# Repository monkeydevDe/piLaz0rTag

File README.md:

# piLaz0rTag

Goto /hardware for fritzing stuff

Goto /code for SourceCode

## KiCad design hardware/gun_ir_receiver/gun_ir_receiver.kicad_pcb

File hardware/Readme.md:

# Hardware

## Shopping List:

* Pi Zero W
* Logic level Converter *https://www.sparkfun.com/products/12009*
* **

## Folders

* **prototype**: Here are the schematics done with fritzing for the breadboard testing.
* **ir_receiver**: Ir receiver module schematics.
* **ir_sender**: Ir sender module schematics.
* **main_board**: Pi Hat module schematics.
* **pi_header**: Template for a pi header.

## Schematics

The schematics are done with the awesome Tool: http://fritzing.org for the prototyping and KiCad for the PCB design.

### Part libraries we used

#### KiCad

* Take a look here: https://kicad.github.io/ !!!!
* As a base for the PL9823 LEDs: https://github.com/madworm/WS2812B.pretty.git
* For the some parts https://github.com/RoboUlbricht/kicad.lib.git
* PiZero hat: https://github.com/help-14/PiZeroHat
* 74AHCT125: https://github.com/propane-and-electrons/kicad-libs
* https://github.com/cfobel/sparkfun_kicad_lib
* https://github.com/benwis/SparkFun-Kicad-Libraries (includes moste of the sparkfun stuff)
* https://www.snapeda.com/parts/L293D/STMicroelectronics/view-part/
* Search for parts: https://easyeda.com/search/level%20bidirectional

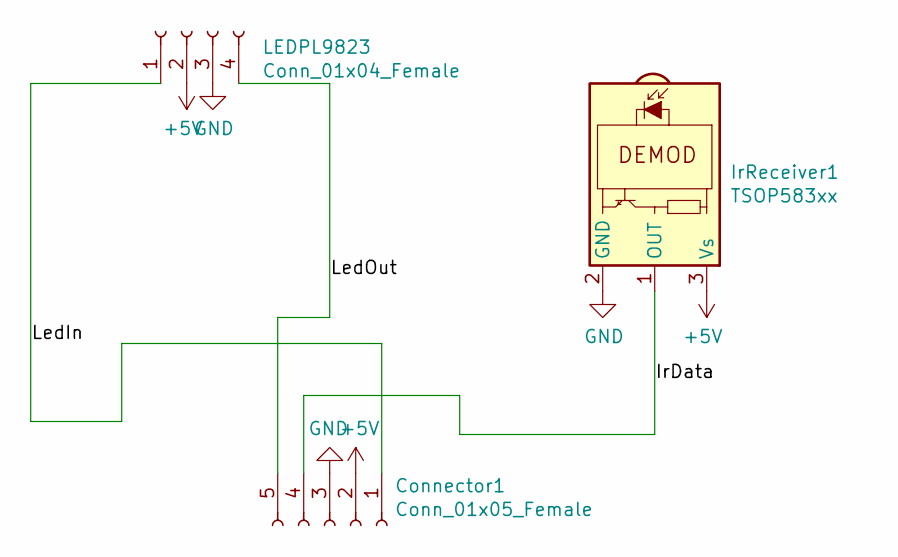
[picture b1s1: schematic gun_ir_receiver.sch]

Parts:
Connector1: Conn_01x05_Female; JST_EH_B05B-EH-A_1x05_P2.50mm_Vertical
IrReceiver1: TSOP583xx; Vishay_MINICAST-3Pin
LEDPL9823: Conn_01x04_Female; PinSocket_1x04_P2.54mm_Vertical

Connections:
+5V: Connector1.2, IrReceiver1.3 (Vs), LEDPL9823.2
/IrData: Connector1.4, IrReceiver1.1 (OUT)
/LedIn: Connector1.1, LEDPL9823.1
/LedOut: Connector1.5, LEDPL9823.4
GND: Connector1.3, IrReceiver1.2 (GND), LEDPL9823.3

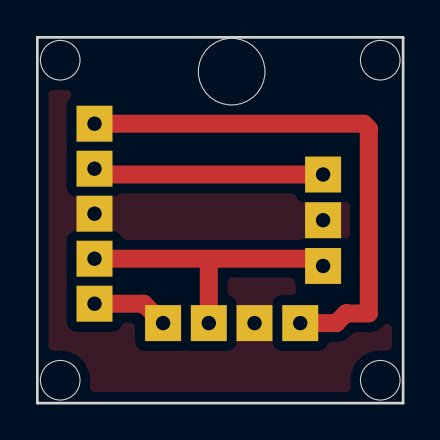
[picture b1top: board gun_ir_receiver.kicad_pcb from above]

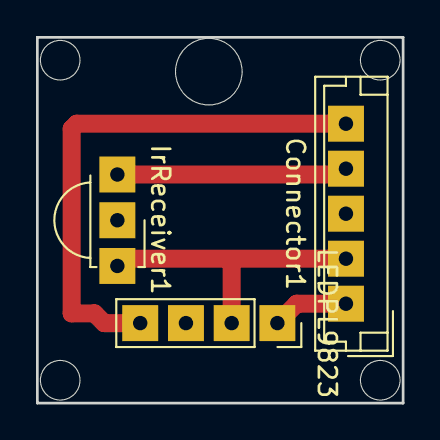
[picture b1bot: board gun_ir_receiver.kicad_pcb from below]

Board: 2 copper layers, 20.3 x 20.3 mm, 6 parts (3 on the bottom side), 5 nets.

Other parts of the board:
Cable Hole: MountingHole_3.7mm
M2, M2#2: MountingHole_2.2mm_M2

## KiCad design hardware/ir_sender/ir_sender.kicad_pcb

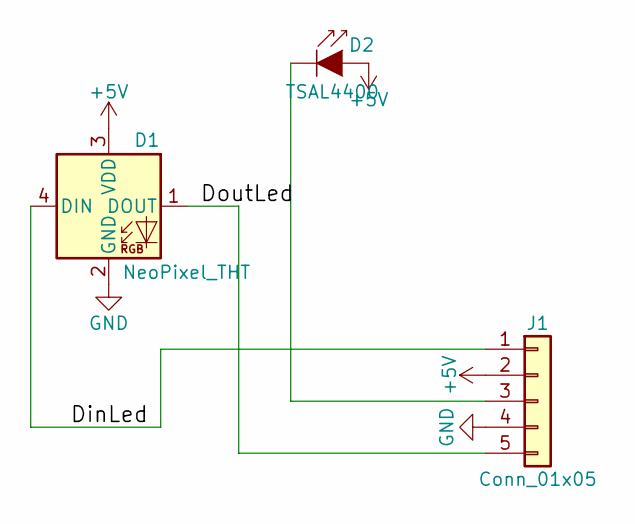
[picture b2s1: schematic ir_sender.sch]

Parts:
D1: NeoPixel_THT; Socket_Strip_Straight_1x04_Pitch2.54mm
D2: TSAL4400; Socket_Strip_Straight_1x02_Pitch2.54mm
J1: Conn_01x05; JST_XH_B05B-XH-A_05x2.50mm_Straight

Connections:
+5V: D1.3 (VDD), D2.2 (A), J1.2
/DinLed: D1.4 (DIN), J1.1
/DoutLed: D1.1 (DOUT), J1.5
GND: D1.2 (GND), J1.4
unnamed: D2.1 (K), J1.3

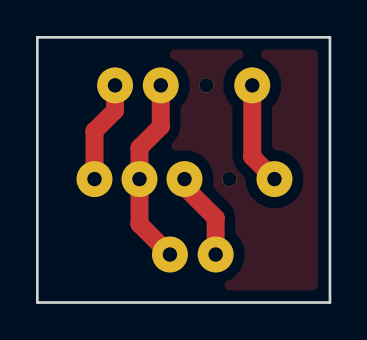
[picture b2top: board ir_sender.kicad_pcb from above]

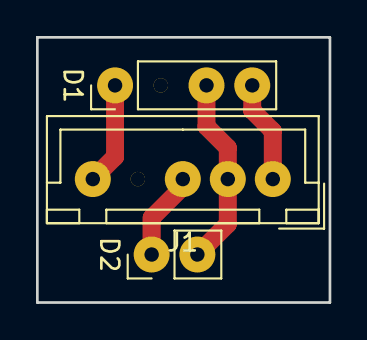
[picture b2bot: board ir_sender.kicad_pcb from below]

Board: 2 copper layers, 16.3 x 14.7 mm, 3 parts (3 on the bottom side), 5 nets.

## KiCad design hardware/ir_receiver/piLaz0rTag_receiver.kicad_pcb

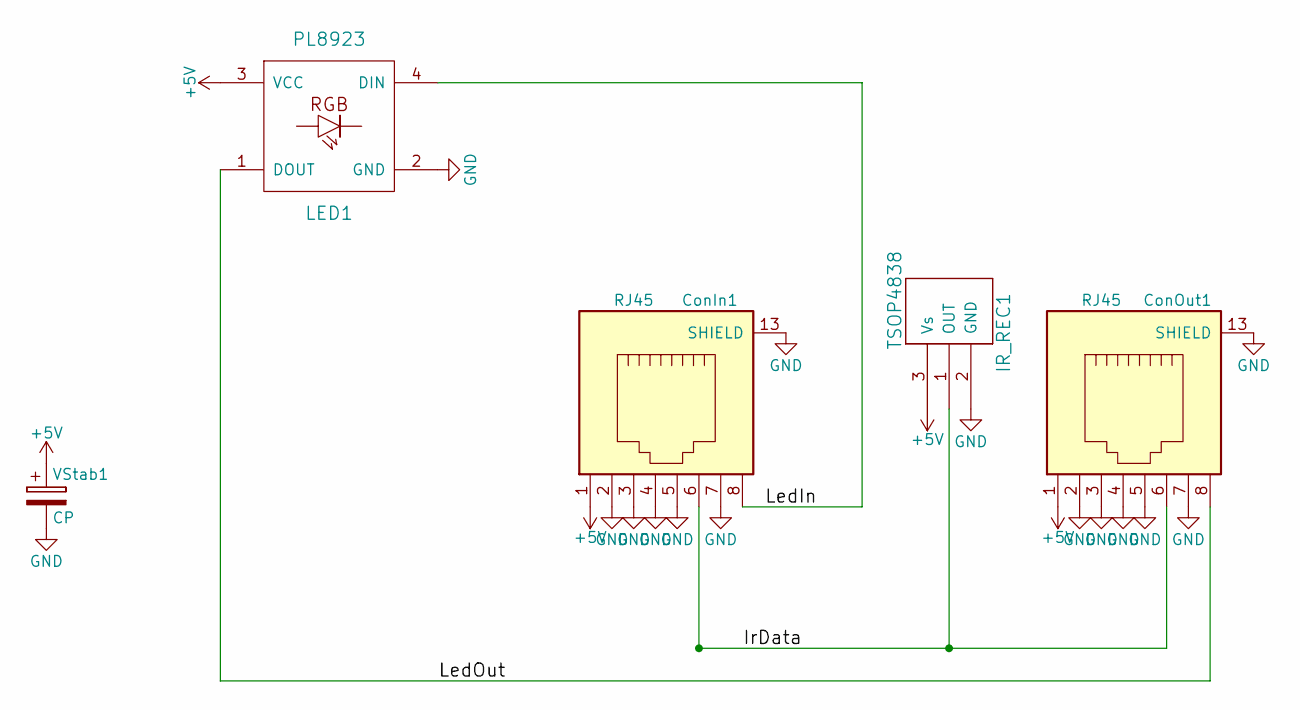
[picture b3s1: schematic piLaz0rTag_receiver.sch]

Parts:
ConIn1: RJ45; rj45-seppel-small
ConOut1: RJ45; rj45-seppel-small
IR_REC1: TSOP4838; IRReceiver_Vishay_MOLD-3pin
LED1: PL8923; Socket_Strip_Straight_1x04_Pitch2.54mm
VStab1: CP; CP_Radial_D4.0mm_P2.00mm

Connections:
+5V: ConIn1.1, ConOut1.1, IR_REC1.3 (Vs), LED1.3 (VCC), VStab1.1
/IrData: ConIn1.6, ConOut1.6, IR_REC1.1 (OUT)
/LedIn: ConIn1.8, LED1.4 (DIN)
/LedOut: ConOut1.8, LED1.1 (DOUT)
GND: ConIn1.2, ConIn1.3, ConIn1.4, ConIn1.5, ConIn1.7, ConIn1.13 (SHIELD), ConOut1.2, ConOut1.3, ConOut1.4, ConOut1.5, ConOut1.7, ConOut1.13 (SHIELD), IR_REC1.2 (GND), LED1.2 (GND), VStab1.2

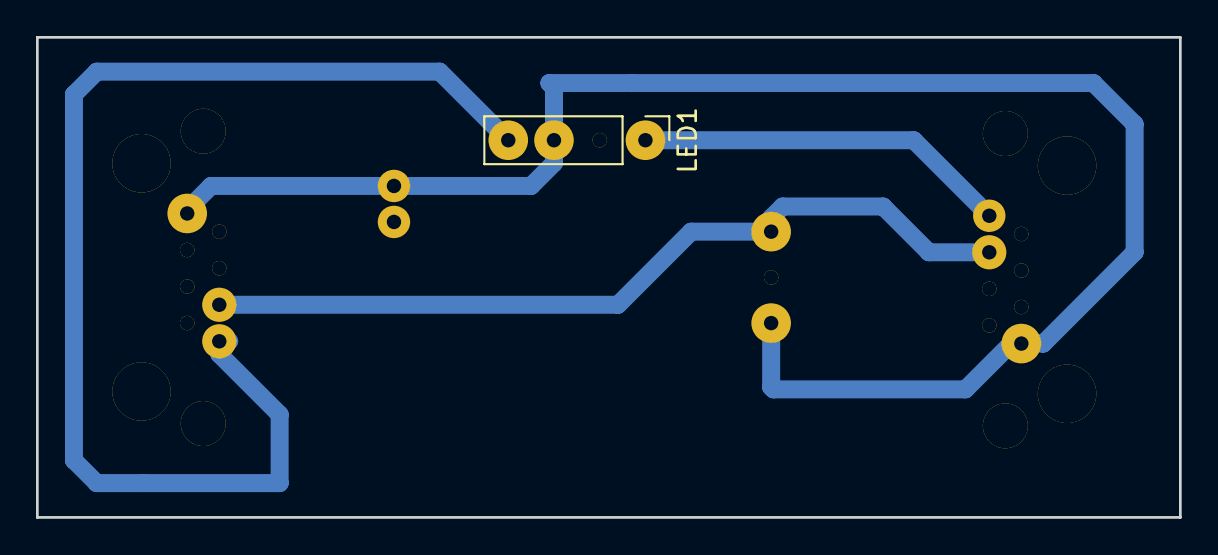
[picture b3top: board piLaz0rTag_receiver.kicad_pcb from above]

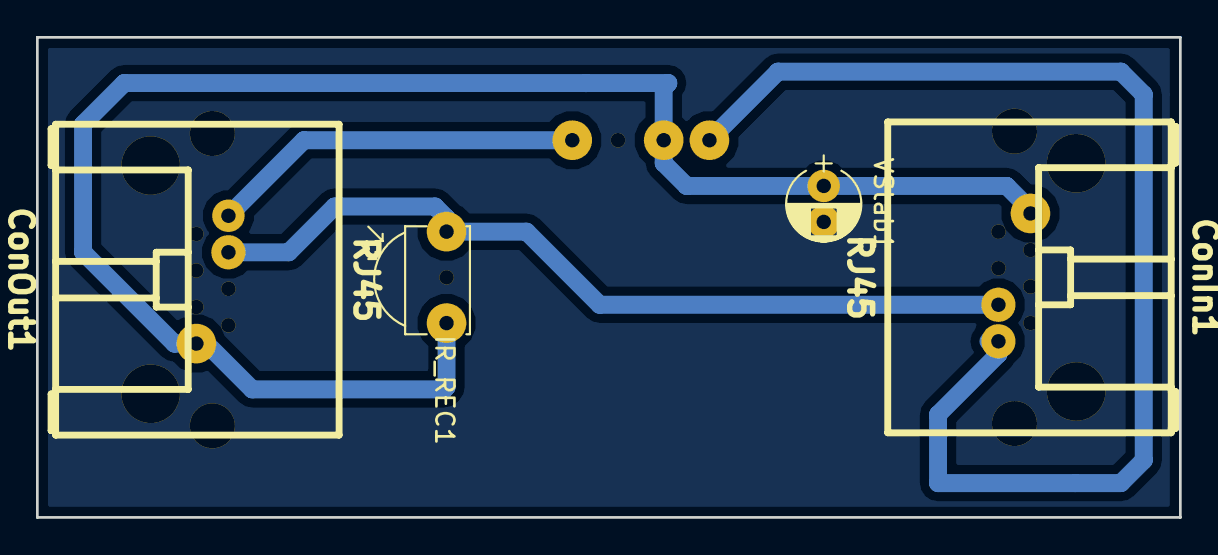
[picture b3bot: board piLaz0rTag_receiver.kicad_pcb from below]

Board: 2 copper layers, 63.5 x 26.7 mm, 5 parts (4 on the bottom side), 5 nets.

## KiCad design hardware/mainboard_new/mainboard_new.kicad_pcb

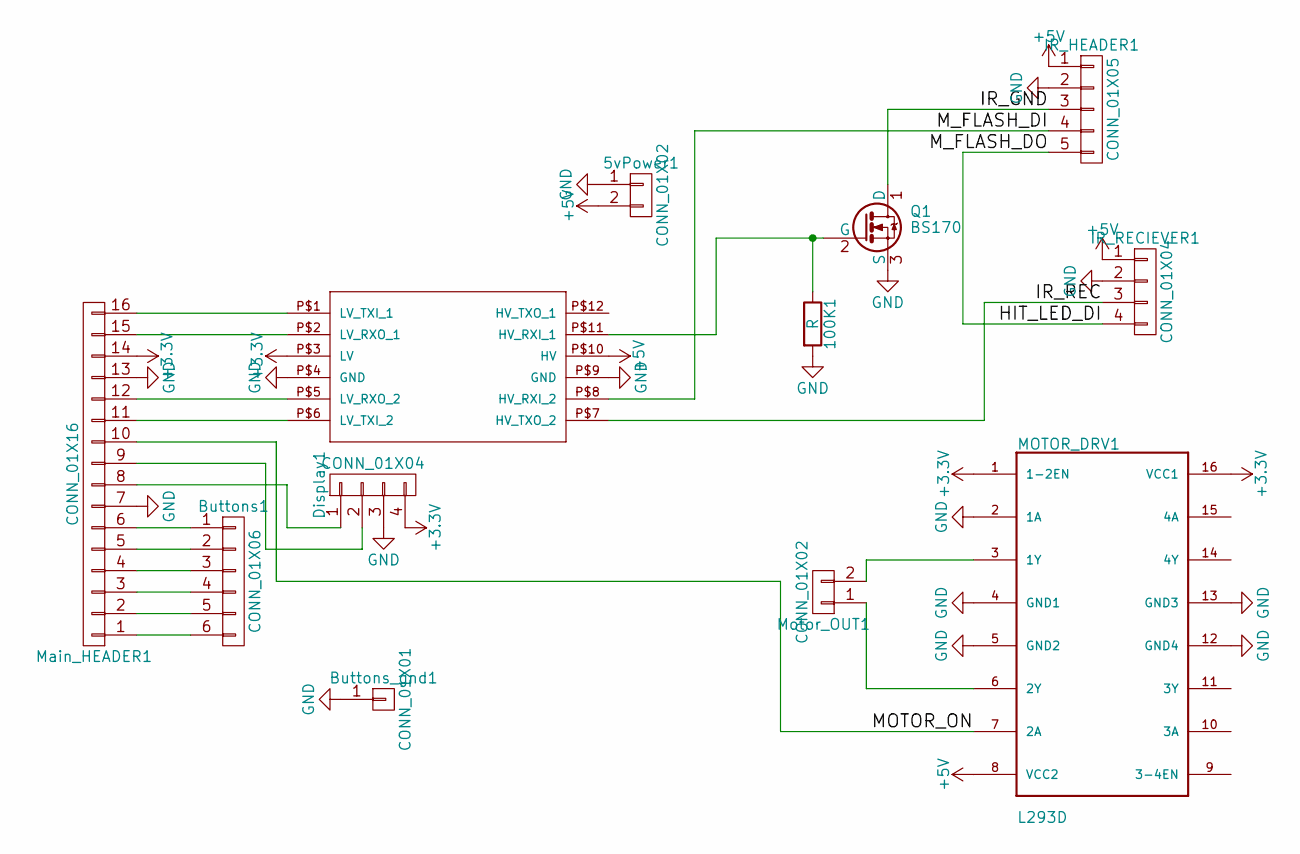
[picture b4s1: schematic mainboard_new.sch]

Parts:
5vPower1: CONN_01X02; JST_EH_B02B-EH-A_02x2.50mm_Straight
100K1: R; R_Axial_DIN0207_L6.3mm_D2.5mm_P10.16mm_Horizontal
Buttons1: CONN_01X06; JST_EH_B06B-EH-A_06x2.50mm_Straight
Buttons_gnd1: CONN_01X01; Socket_Strip_Straight_1x01_Pitch1.27mm
Display1: CONN_01X04; JST_EH_B04B-EH-A_04x2.50mm_Straight
IR_HEADER1: CONN_01X05; JST_EH_B05B-EH-A_05x2.50mm_Straight
IR_RECIEVER1: CONN_01X04; JST_EH_B04B-EH-A_04x2.50mm_Straight
M1: LOGIC_LEVEL_CONVERTER
MOTOR_DRV1: L293D; DIL16
Main_HEADER1: CONN_01X16; Socket_Strip_Straight_1x16_Pitch2.54mm
Motor_OUT1: CONN_01X02; Socket_Strip_Straight_1x02_Pitch2.54mm
Q1: BS170; TO-92_Inline_Wide

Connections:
+3V3: Display1.4, M1.P$3 (LV), MOTOR_DRV1.1 (1-2EN), MOTOR_DRV1.16 (VCC1), Main_HEADER1.14
+5V: 5vPower1.2, IR_HEADER1.1, IR_RECIEVER1.1, M1.P$10 (HV), MOTOR_DRV1.8 (VCC2)
/HIT_LED_DI: IR_HEADER1.5, IR_RECIEVER1.4
/IR_GND: IR_HEADER1.3, Q1.1 (D)
/IR_REC: IR_RECIEVER1.3, M1.P$7 (HV_TXO_2)
/MOTOR_ON: MOTOR_DRV1.7 (2A), Main_HEADER1.10
/M_FLASH_DI: IR_HEADER1.4, M1.P$8 (HV_RXI_2)
GND: 5vPower1.1, 100K1.2, Buttons_gnd1.1, Display1.3, IR_HEADER1.2, IR_RECIEVER1.2, M1.P$4 (GND), M1.P$9 (GND), MOTOR_DRV1.2 (1A), MOTOR_DRV1.4 (GND1), MOTOR_DRV1.5 (GND2), MOTOR_DRV1.12 (GND4), MOTOR_DRV1.13 (GND3), Main_HEADER1.7, Main_HEADER1.13, Q1.3 (S)
unnamed: 100K1.1, M1.P$11 (HV_RXI_1), Q1.2 (G)
unnamed: Buttons1.1, Main_HEADER1.6
unnamed: Buttons1.2, Main_HEADER1.5
unnamed: Buttons1.3, Main_HEADER1.4
unnamed: Buttons1.4, Main_HEADER1.3
unnamed: Buttons1.5, Main_HEADER1.2
unnamed: Buttons1.6, Main_HEADER1.1
unnamed: Display1.1, Main_HEADER1.8
unnamed: Display1.2, Main_HEADER1.9
unnamed: M1.P$1 (LV_TXI_1), Main_HEADER1.16
unnamed: M1.P$2 (LV_RXO_1), Main_HEADER1.15
unnamed: M1.P$5 (LV_RXO_2), Main_HEADER1.12
unnamed: M1.P$6 (LV_TXI_2), Main_HEADER1.11
unnamed: MOTOR_DRV1.3 (1Y), Motor_OUT1.2
unnamed: MOTOR_DRV1.6 (2Y), Motor_OUT1.1

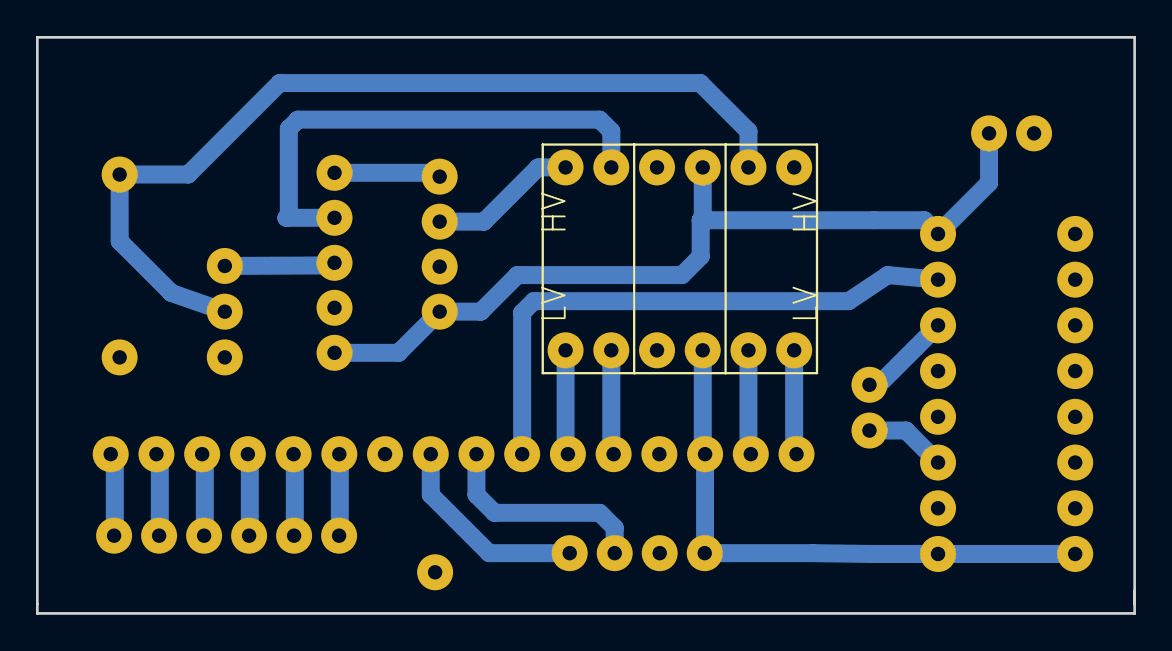
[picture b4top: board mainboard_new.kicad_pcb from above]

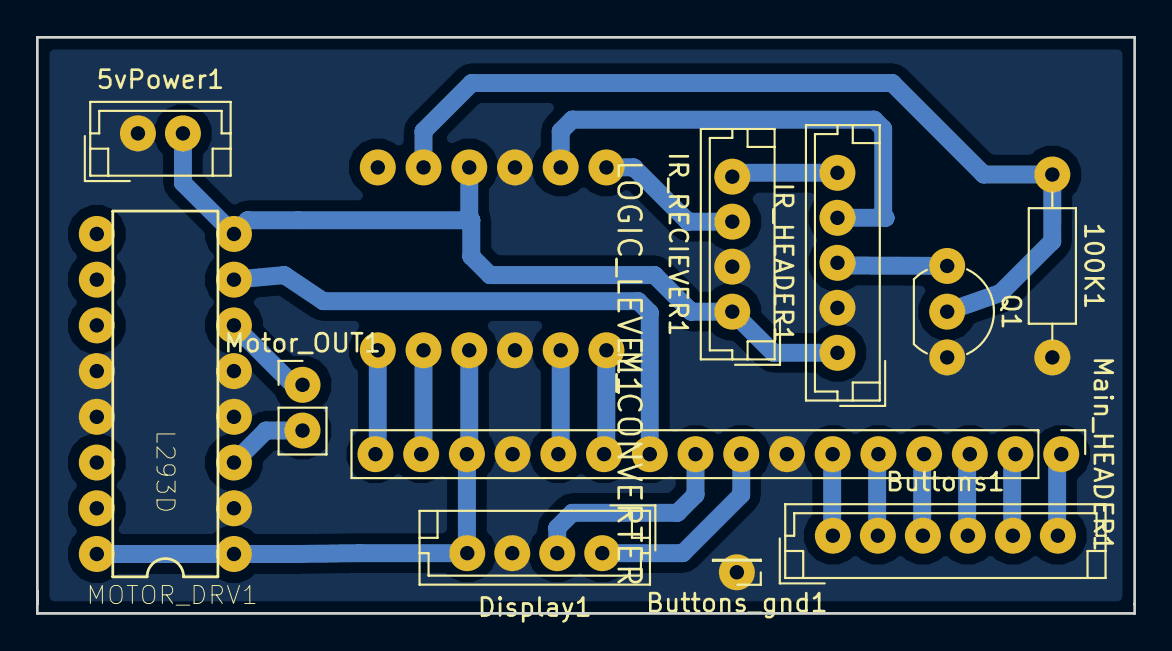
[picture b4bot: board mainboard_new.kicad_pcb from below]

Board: 2 copper layers, 61.0 x 32.0 mm, 12 parts (12 on the bottom side), 23 nets.

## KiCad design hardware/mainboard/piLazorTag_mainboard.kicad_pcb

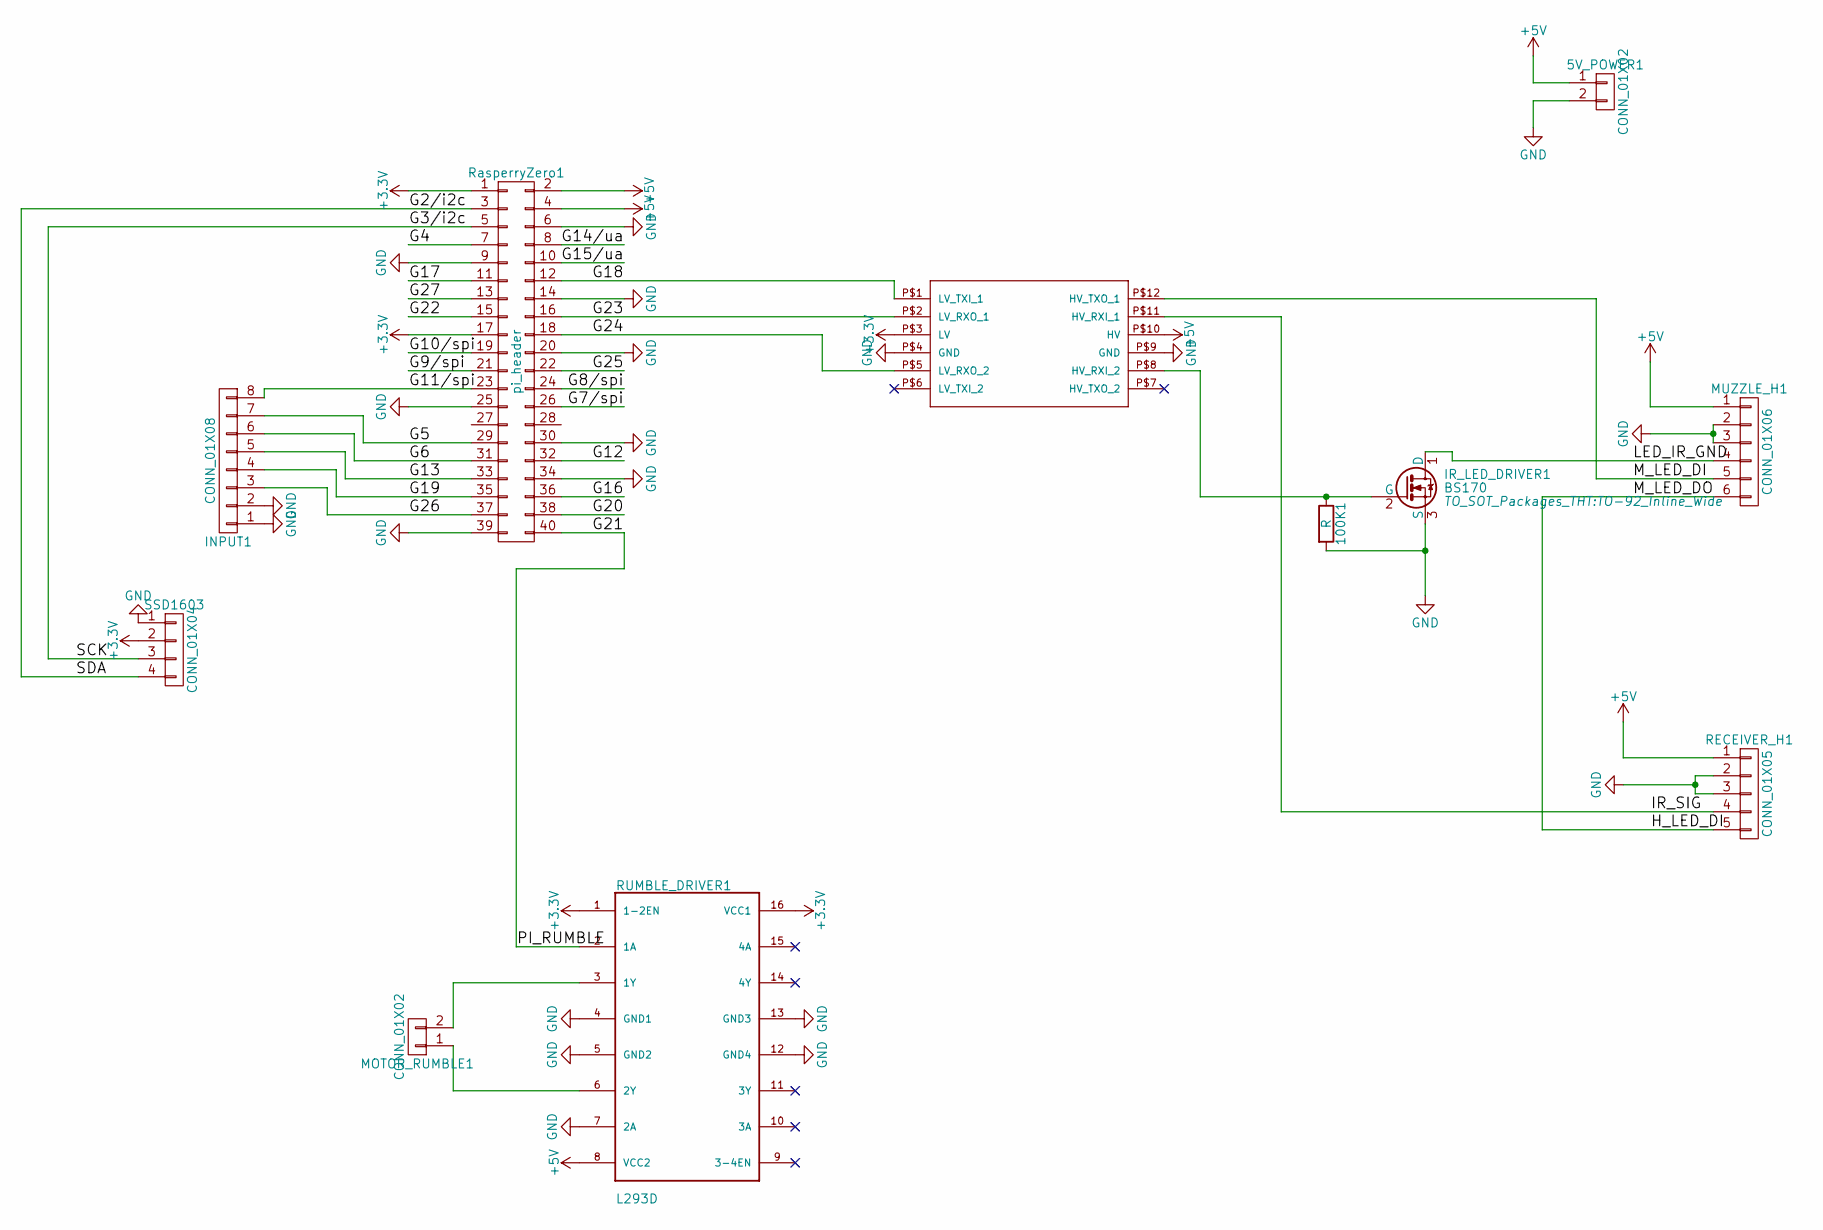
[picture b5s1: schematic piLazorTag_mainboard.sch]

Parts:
5V_POWER1: CONN_01X02; Pin_Header_Straight_2x01_Pitch2.54mm
100K1: R; R_Axial_DIN0207_L6.3mm_D2.5mm_P10.16mm_Horizontal
INPUT1: CONN_01X08; Pin_Header_Straight_1x08_Pitch2.54mm
IR_LED_DRIVER1: BS170; TO-92_Inline_Wide
M1: LOGIC_LEVEL_CONVERTER
MOTOR_RUMBLE1: CONN_01X02; Pin_Header_Straight_1x02_Pitch2.54mm
MUZZLE_H1: CONN_01X06; Pin_Header_Straight_1x06_Pitch2.54mm
RECEIVER_H1: CONN_01X05; Pin_Header_Straight_1x05_Pitch2.54mm
RUMBLE_DRIVER1: L293D; DIL16
RasperryZero1: pi_header; Pin_Header_Straight_2x20_Pitch2.54mm
SSD1603: CONN_01X04; Pin_Header_Straight_1x04_Pitch2.54mm

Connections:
+3V3: M1.P$3 (LV), RUMBLE_DRIVER1.1 (1-2EN), RUMBLE_DRIVER1.16 (VCC1), RasperryZero1.1, RasperryZero1.17, SSD1603.2
+5V: 5V_POWER1.1, M1.P$10 (HV), MUZZLE_H1.1, RECEIVER_H1.1, RUMBLE_DRIVER1.8 (VCC2), RasperryZero1.2, RasperryZero1.4
/G2/i2c: RasperryZero1.3, SSD1603.4
/G3/i2c: RasperryZero1.5, SSD1603.3
/G4: RasperryZero1.7
/G5: INPUT1.7, RasperryZero1.29
/G6: INPUT1.6, RasperryZero1.31
/G7/spi: RasperryZero1.26
/G8/spi: RasperryZero1.24
/G9/spi: RasperryZero1.21
/G10/spi: RasperryZero1.19
/G11/spi: INPUT1.8, RasperryZero1.23
/G12: RasperryZero1.32
/G13: INPUT1.5, RasperryZero1.33
/G14/ua: RasperryZero1.8
/G15/ua: RasperryZero1.10
/G16: RasperryZero1.36
/G17: RasperryZero1.11
/G18: M1.P$1 (LV_TXI_1), RasperryZero1.12
/G19: INPUT1.4, RasperryZero1.35
/G20: RasperryZero1.38
/G21: RUMBLE_DRIVER1.2 (1A), RasperryZero1.40
/G22: RasperryZero1.15
/G23: M1.P$2 (LV_RXO_1), RasperryZero1.16
/G24: M1.P$5 (LV_RXO_2), RasperryZero1.18
/G25: RasperryZero1.22
/G26: INPUT1.3, RasperryZero1.37
/G27: RasperryZero1.13
/H_LED_DI: MUZZLE_H1.6, RECEIVER_H1.5
/IR_SIG: M1.P$11 (HV_RXI_1), RECEIVER_H1.4
/LED_IR_GND: IR_LED_DRIVER1.1 (D), MUZZLE_H1.4
/M_LED_DI: M1.P$12 (HV_TXO_1), MUZZLE_H1.5
GND: 5V_POWER1.2, 100K1.2, INPUT1.1, INPUT1.2, IR_LED_DRIVER1.3 (S), M1.P$4 (GND), M1.P$9 (GND), MUZZLE_H1.2, MUZZLE_H1.3, RECEIVER_H1.2, RECEIVER_H1.3, RUMBLE_DRIVER1.4 (GND1), RUMBLE_DRIVER1.5 (GND2), RUMBLE_DRIVER1.7 (2A), RUMBLE_DRIVER1.12 (GND4), RUMBLE_DRIVER1.13 (GND3), RasperryZero1.6, RasperryZero1.9, RasperryZero1.14, RasperryZero1.20, RasperryZero1.25, RasperryZero1.30, RasperryZero1.34, RasperryZero1.39, SSD1603.1
unnamed: 100K1.1, IR_LED_DRIVER1.2 (G), M1.P$8 (HV_RXI_2)
unnamed: MOTOR_RUMBLE1.1, RUMBLE_DRIVER1.6 (2Y)
unnamed: MOTOR_RUMBLE1.2, RUMBLE_DRIVER1.3 (1Y)

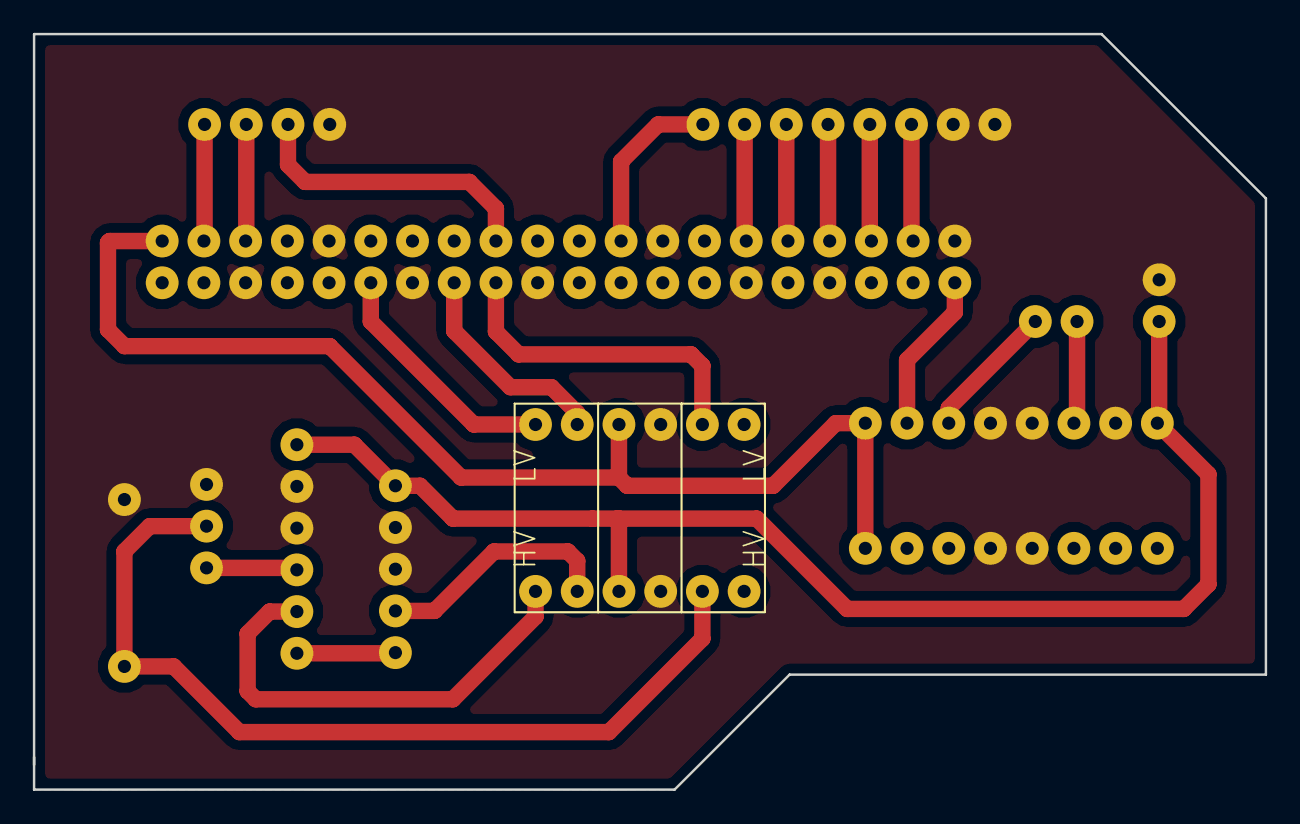
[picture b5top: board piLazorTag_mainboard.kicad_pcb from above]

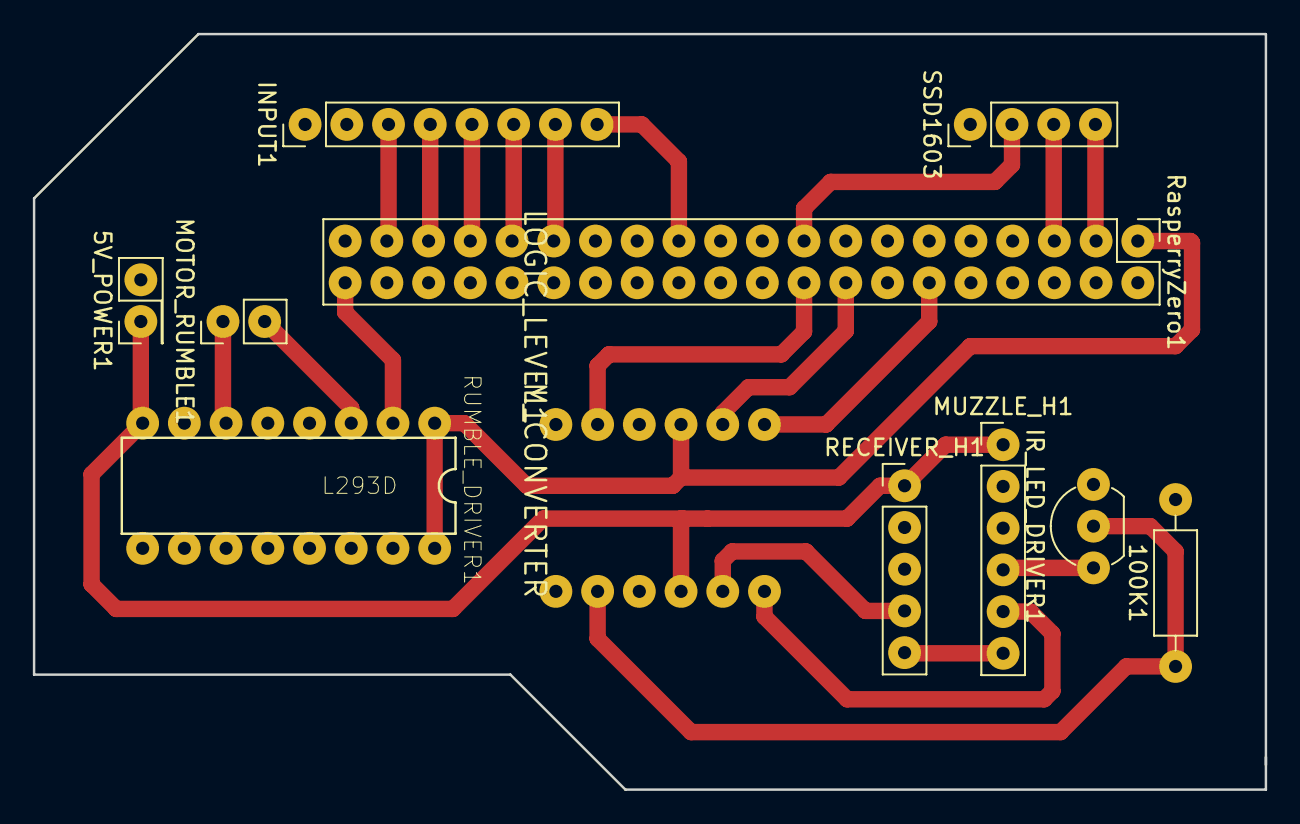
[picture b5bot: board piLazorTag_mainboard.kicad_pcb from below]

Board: 2 copper layers, 75.0 x 46.0 mm, 11 parts (11 on the bottom side), 22 nets.

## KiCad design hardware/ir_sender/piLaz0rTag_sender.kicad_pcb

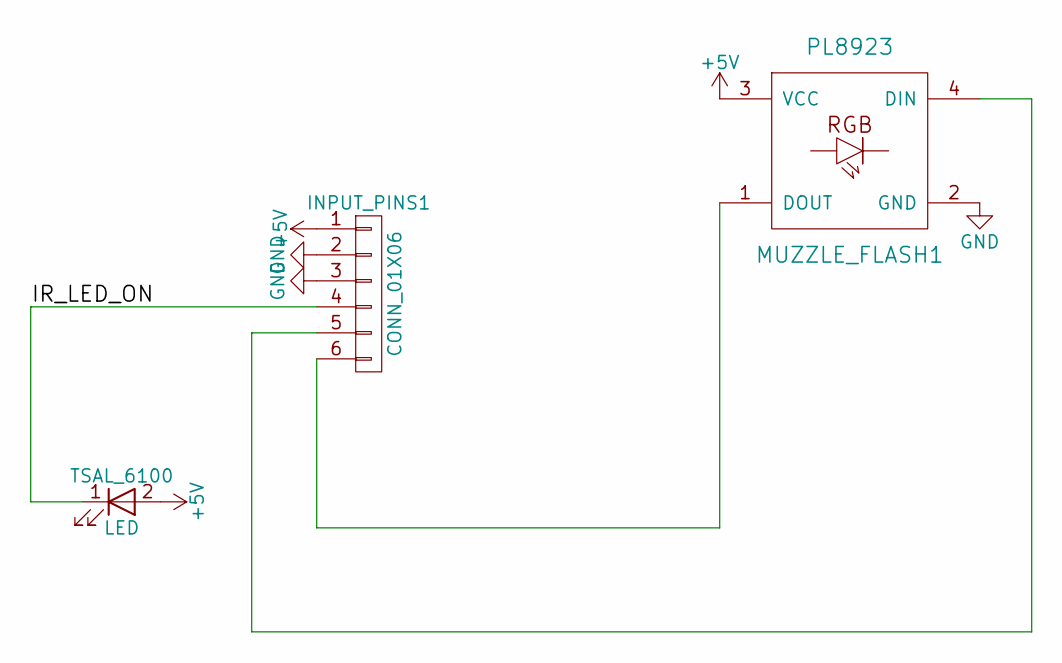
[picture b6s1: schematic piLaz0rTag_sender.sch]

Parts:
INPUT_PINS1: CONN_01X06; Socket_Strip_Straight_1x06_Pitch2.54mm
MUZZLE_FLASH1: PL8923; Socket_Strip_Straight_1x04_Pitch2.54mm
TSAL_6100: LED; LED_D5.0mm

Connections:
+5V: INPUT_PINS1.1, MUZZLE_FLASH1.3 (VCC), TSAL_6100.2 (A)
/IR_LED_ON: INPUT_PINS1.4, TSAL_6100.1 (K)
GND: INPUT_PINS1.2, INPUT_PINS1.3, MUZZLE_FLASH1.2 (GND)
unnamed: INPUT_PINS1.5, MUZZLE_FLASH1.4 (DIN)
unnamed: INPUT_PINS1.6, MUZZLE_FLASH1.1 (DOUT)

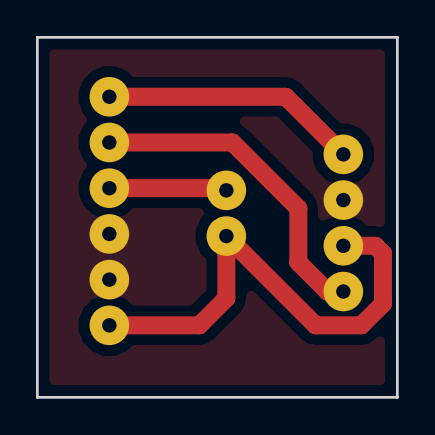
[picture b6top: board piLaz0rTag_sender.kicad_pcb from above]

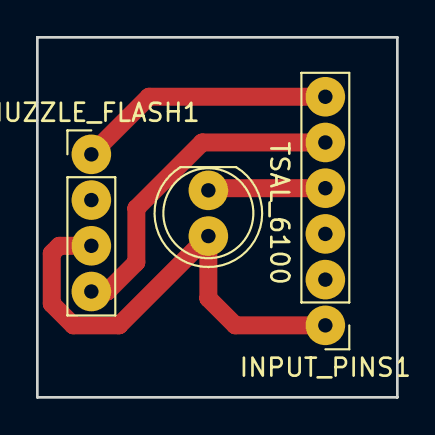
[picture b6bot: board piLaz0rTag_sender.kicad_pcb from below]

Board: 2 copper layers, 20.0 x 20.0 mm, 3 parts (3 on the bottom side), 5 nets.

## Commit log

2017-03-25 Start to add strucuture
2017-03-25 Add first gun schemantic
2017-03-25 Add the first breadboard layout
2017-03-30 add folder n structure for code add gitignore add settings.js module add display.js module add primary js -> piLaz0rTag.js
2017-04-05 add standard.js for defining enum like values for global use, add logging.js for simple custom app logging, change display.js to use a parent display obj to display.js with prototypes change display.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
2017-04-07 add standards about game actions + Menu events add standards about device stats
2017-04-07 add primary vars and extend init of event handling
2017-04-07 add display prototype init initial menu to display.js add menuHandler to piLaz0rTag.js
2017-04-07 add some commas
2017-04-10 Some documentation added
2017-04-10 Add package json
2017-04-10 Add rpi-ws281x-native as node dependency
2017-04-10 Add nodemon
2017-04-10 Add start via nodemon
2017-04-10 Add missing ,
2017-04-10 Add https://github.com/NeinsKnull/oled_ssd1306_i2c as dependency
2017-04-10 Add some basic keyboard handler
2017-04-11 change comments (cosmetic)
2017-04-11 add the ParentDisplay.prototype functionality to init an initial menu an print the screen for display
2017-04-12 Add test lircd.conf using milestag protocoll
2017-04-12 Removed ending space so it can be parsed by lircd.
2017-04-12 Add a functional test lircd file
2017-04-12 #1 start implementing the lircd.conf generator
2017-04-12 #1 Generate the correct hex codes
2017-04-12 #1 Add some documentation
2017-04-12 #1 Add a .gitignore file for the generated file
2017-04-12 #1 Add a Readme.md for the tool
2017-04-12 #2 Start to implement a lircd handler
2017-04-13 #2 Start to change to es6
2017-04-13 #2 Better es6 class handling
2017-04-13 #2 Add winston as logger
2017-04-13 #2 Add description for soundcard setup
2017-04-14 #2 first try with audio not so good so far
2017-04-14 #4 Add Weberser and move some modules to singleton
2017-04-14 #4 refactor the input libary to get web ready
2017-04-14 #4 Start to add socket.io
2017-04-14 #4 We can shot now via websocket
2017-04-14 #4 IR data sending is now better
2017-04-14 #4 Shoot now triggers from web socket to ir :)
2017-04-14 Make the logger level setable in a config
2017-04-15 #6 Start to add the game deathmatch
2017-04-15 #6 Reloading and Shooting is working rudamantary
2017-04-15 #6 Simple webfrontend is getting done
2017-04-15 #6 Reloading works now
2017-04-15 #6 Better web view for the data
2017-04-15 #6 Some cleanup
2017-04-15 #6 Hit is now handled
2017-04-15 #6 Add a simple respawn mechamism
2017-04-15 #6 Better player status handling
2017-04-15 #6 POC for teamdeathmacht mode
2017-04-15 #6 add a game setup html page
2017-04-15 #6 Start the game via the webinterface
2017-04-15 #6 Start game is working now
2017-04-15 #6 Start and stop game over events
2017-04-15 #6 Started adding LEDS
2017-04-17 add a ir mock
2017-04-17 add instance to the sendShootMsg in IrMockHandler
2017-04-18 #11 Start pcb layout for ir receiver
2017-04-18 #11 Readme and move gun directory
2017-04-18 #9 start pi hat
2017-04-18 #9 Add gerber files
2017-04-19 #9 Add some kicad files for pi hat
2017-04-19 #9 Add a mainboard kicad project
2017-04-19 #9 Add mainboard
2017-04-19 #9 Add some header for the connectors
2017-04-19 #9 New layout with pi header
2017-04-19 Add a Websockt Ir handler so the user can simulate ir received signals
2017-04-19 #25 Better handling for events
2017-04-19 #25 Rework of eventhandler finished
2017-04-19 #25 Add Enable Disable Event Debug
2017-04-19 #5 LED Server is working now
2017-04-19 #5 Start Ws2812 Client implementation
2017-04-22 #5 some blinking added
2017-04-23 #5 Get Leds working
2017-04-24 #5 Led blink now correctly and are managed by the game
2017-04-24 #5 Normal Game also emits led
2017-04-28 #28 Start to add basic rumble factory
2017-04-28 #28 basic rumble with motor added when shooting
2017-04-28 #28 web rumble via vibrate api
2017-04-28 Some housekeeping
2017-04-28 #31 Load all the modules via the registry
2017-04-28 No need for standard.js anymore
2017-04-28 Settings is now a class
2017-04-29 #3 Sound support for local files
2017-04-29 #3 Event was at the wrong place
2017-04-30 I2C setup
2017-04-30 Start to add SSD1360 code
2017-04-30 #34 Add a way to override settings vie json file
2017-04-30 Make some module be always loaded
2017-04-30 SSD1360 rudemantary added
2017-04-30 Make the pi deps optional
2017-04-30 Webfrontend now handles connect and disconnect of socket with blockui
2017-05-02 Some rework on the ir receiver pcb
2017-05-03 Add i2cdetect
2017-05-03 SSD1306 is now in a seperate process
2017-05-03 Some better handling when restarting the game
2017-05-05 #9 Ir Receiver
2017-05-05 #9 Gerber files
2017-05-06 Add ir sender gerber files
2017-05-06 #9 mainboard schemantics
2017-05-06 Add a script which downloads the kicad libs from github
2017-05-06 Some minor changes on the receiver mainboard
2017-05-06 #9 First net generated for mainboard
2017-05-07 #9 Reasigned some pins to get a better board layout
2017-05-07 #37 start adding new gpio input module
2017-05-08 #9 Further Progress on the mainboard
2017-05-08 #37 Shooting and reloading works over gpio
2017-05-08 #9 More work on the mainboard
2017-05-08 Unique Player id is now the hostname
2017-05-08 Add mainstates as an object
2017-05-08 Moved websocket msg handling for game into own class
2017-05-11 #9 first Mainbaordlayout done
2017-05-11 #9 Start to change pad layout
2017-05-12 Some rework on the receiver pcb
2017-05-12 Receiver Layout
2017-05-12 Receiver
2017-05-13 #12 Start ir receiver housing openscad file
2017-05-13 #12 Add screw holes
2017-05-13 #12 Add bottom clamp
2017-05-13 #40 Add a simple lens holder
2017-05-13 #40 Add the lens holder ring
2017-05-13 #40 Set resolution to 100
2017-05-13 #40 Set Add ir sender slit
2017-05-14 Made it smaller
2017-05-14 #40 more work on the lensholder
2017-05-14 Ir Sender Pcb added
2017-05-14 Real dims
2017-05-15 Some better WS2812 handling using websockets
2017-05-15 Add Gameover
2017-05-15 Start to add weapon modes single,semi,full
2017-05-15 Preps for refactoring Player
2017-05-17 Start adding master mode
2017-05-17 #42 Start refactoring html gui
2017-05-17 #42 Start adding client and master mode
2017-05-17 #42 Constructor clean up of the express webserver
2017-05-18 #42 start to change mode changes
2017-05-19 Add some brackouts to the lower section
2017-05-19 Move modes to states
2017-05-20 Some new sender gerber stuff
2017-05-20 Some work on the 3dfiles
2017-05-20 Some changes in the gcode
2017-05-20 Test for 2.2 holes
2017-05-22 #42 Master Client is getting cleaner
2017-05-22 #42 Better Client handling
2017-05-22 #42 some more rework
2017-05-22 #42 First layout for a client
2017-05-22 #42 Fields fire update onchange now
2017-05-22 #42 Start to add start game for master and client
2017-05-22 #42 Game Starting state added
2017-05-22 #42 Game Running start
2017-05-23 #42 Game Running Gui
2017-05-23 #42 removed old gui
2017-05-23 Better lens holder
2017-05-27 #13 Better Lensholder
2017-05-28 ClientMode is now ClientState
2017-05-28 Some rework on the lens holder
2017-05-28 Add Gui ClientStateHandler
2017-05-28 When client is ended disconnect from the server
2017-05-28 Auto focus field when master gui was renderd
2017-05-28 Handle Client data request
2017-05-28 This is not an instance
2017-05-28 Add missing # for id in Client gui
2017-05-29 #8 Start to add bonjour
2017-06-10 Fix this is an instance
2017-06-10 #9 gcode generated
2017-06-10 #8 make the name unique
2017-06-10 #8 Welcomehandler in the gui
2017-06-10 #8 Unique id
2017-06-10 #8 Unique id is now better
2017-07-01 #10 gcode for cyclone generated
2017-07-01 Some changes in the lensholder
2017-07-01 Some changes
2017-07-05 Better ssd1306 display handling
2017-07-12 #9 New mainboard
2017-07-14 #9 More rework at the pcb
2017-07-14 #9 Moved gcode
2017-07-15 #9 JST Pins added
2018-05-13 Add rj45 shield
2018-05-14 Start adding rj45 connectoren
2018-05-14 Add ir adjuster
2018-05-14 Start fixing to real sizes
2018-05-14 Back dimensions
2018-05-14 Add new lens holder which is put into the tube
2018-05-14 Some minor changes at the lens holder
2018-05-15 Some rework on the led holder
2018-05-16 Make the led ring holes on the correct side
2018-05-17 Add Dome as drawing
2018-05-17 More work on the receiver with rj45
2018-05-17 First thing to test
2018-05-18 Make GND also in schemantic
2018-05-18 Add cuts and adj point
2018-05-18 Some rework before putting it on the cnc
2018-05-18 Fix brocken cnc stuff
2018-05-19 Add drill hole for fresnel lens
2018-05-19 Add rj45 connector board
2018-05-19 Flipped the mainbaord
2018-05-19 Clean up not needed hardware files
2018-05-19 Some gcode
2018-05-19 New better receiver layout file
2018-05-19 Some more changes for the cnc
2018-05-25 Start adding pcb for ir sender
2018-05-26 New ir sender board
2018-05-26 Start to add PCB ir sender holder
2018-05-26 Some more work on the ir sender pcb holder
2018-05-26 More space on the ir sender pcb
2018-05-26 Start adding pcb ir holder adjuste
2018-05-27 Correct the pcb height
2018-05-27 Add gcode
2018-11-21 Added some new ir receiver board
2018-11-21 Added led
2018-11-25 Some fixes at the ir adjuster
2018-11-29 Added gerber files
2018-11-29 Added gcode
2018-12-03 New Mainboard
2018-12-09 Add Gun ir receiver housing
2018-12-10 Start adding input connectors
2019-01-05 Starting tagger model
2019-01-05 Some more work on the tagger
2019-01-05 Add hole where the grip is attached to the body
2019-01-06 Start Esp32 pcb standoff
2019-01-07 Better Body
2019-01-07 Started adding some connector poles
2019-01-07 Started adding speaker
2019-01-08 Grip Body is now handeld better
2019-01-08 Added speaker holder to model
2019-01-08 Added speaker grill
2019-01-08 Make pcb standoff own module
2019-01-08 Fix display holder
2019-01-08 Started trigger mechamism
2019-01-08 Added trigger base
2019-01-09 Better trigger handling
2019-01-09 Housing fixes
2019-01-10 Some rework on the trigger holder lets print it :)
2019-01-10 Add Vibration motor pcb standoff
2019-01-10 Make the wall thinner
2019-01-10 Fix trigger guidance
2019-01-10 added trigger spring pin
2019-01-10 Add screw holes to ir receiver pcb
2019-01-10 Generated gcode for the cnc machine
2019-01-11 Add Receiver cut out
2019-01-22 Started making trigger a general button module
2019-01-22 Button handling is now better
2019-01-23 Added reload button to grip
2019-01-23 More work on the pcb
2019-02-17 Start adding screw holes in the reload button guidance
2019-02-17 Added fix hole for the trigger and reload guidance
2019-09-22 Started work for nerf gun modifications
2019-09-24 Some mor works on the rings
2019-09-25 Remassured the rings
2019-09-29 Added rail thingi
